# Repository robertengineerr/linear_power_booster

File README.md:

# Linear Power Booster | Guitar Pedal
Linear guitar signal booster with BJT amplification, true bypass switching, and power input protection.

BJT Amplifier
This is the core amplification stage. A single NPN BJT (Q1) amplifies the input signal from a guitar or similar audio source. Capacitors C1 and C2 act as AC coupling (DC-blocking) caps, allowing only the AC signal through. R1 and R2 form a voltage divider to bias the base of Q1, while R3 sets emitter current for gain stability. The amplified signal is output through C2, with a variable resistor (RV1) used to control output volume. This design provides a clean linear boost to the input signal.

Power
This section manages power input and protection. It accepts either a 9V barrel jack or battery input, with diode D2 preventing reverse polarity damage. The capacitor C3 provides basic filtering to smooth out voltage spikes, and the TVS0500DRV IC (U1) protects downstream components from overvoltage by clamping any input above ~9V. The design ensures safe and clean power delivery to the circuit.

Bypass System
This section allows toggling between the amplified signal and the unprocessed (dry) signal. It uses a 3PDT switch (S1) to route the signal either through the amplifier or directly from input to output. Capacitor C4 provides AC coupling for the bypassed signal. This system is commonly used in audio pedals to allow true bypass functionality, preserving the original signal when the effect is disengaged.

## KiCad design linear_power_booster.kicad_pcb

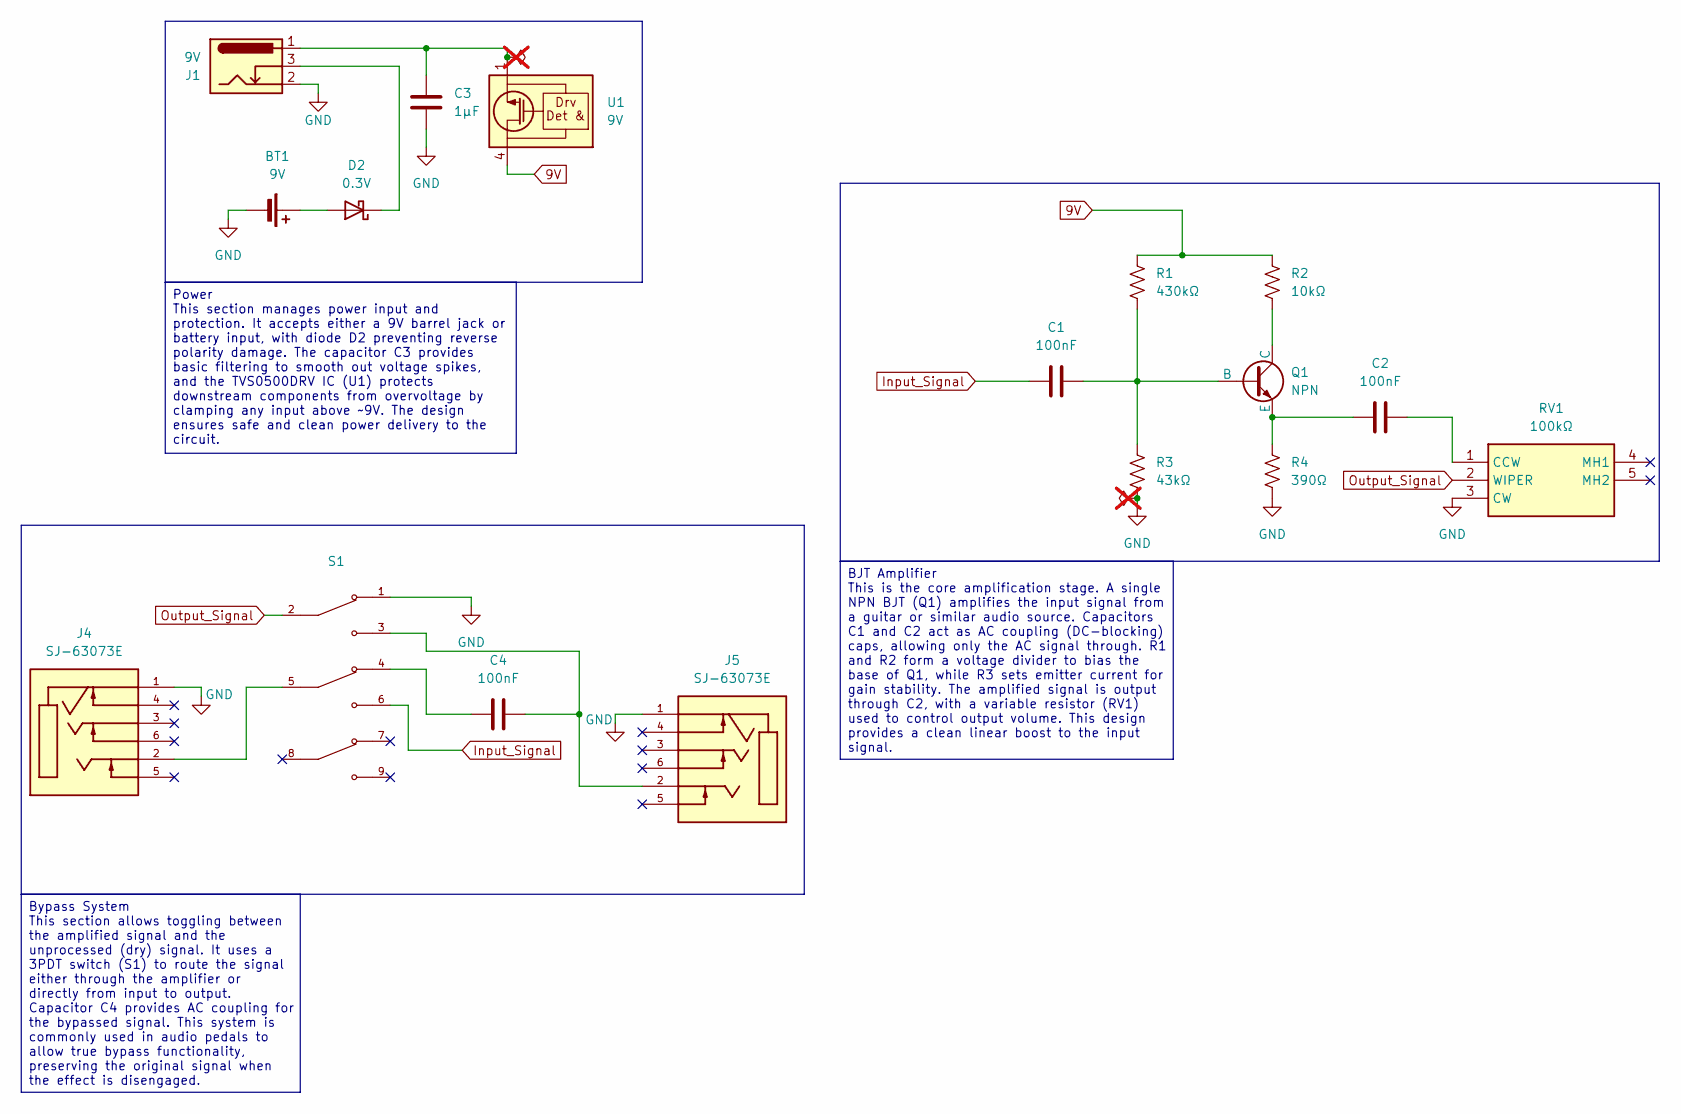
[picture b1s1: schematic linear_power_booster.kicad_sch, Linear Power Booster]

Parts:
BT1: 9V; BatteryHolder_Eagle_12BH611-GR
C1, C2, C4: 100nF; C_Disc_D5.0mm_W2.5mm_P2.50mm
C3: 1µF; C_Disc_D5.0mm_W2.5mm_P2.50mm
D2: 0.3V; D_SMB
J1: 9V; BarrelJack_CUI_PJ-079BH_Horizontal
J4, J5: SJ-63073E; CUI_SJ-63073E; PARTREV 1.0
Q1: NPN; TO-92_Inline
R1: 430kΩ; R_Axial_DIN0207_L6.3mm_D2.5mm_P10.16mm_Horizontal
R2: 10kΩ; R_Axial_DIN0207_L6.3mm_D2.5mm_P10.16mm_Horizontal
R3: 43kΩ; R_Axial_DIN0207_L6.3mm_D2.5mm_P10.16mm_Horizontal
R4: 390Ω; R_Axial_DIN0207_L6.3mm_D2.5mm_P10.16mm_Horizontal
RV1: 100kΩ; PTV09A4030FA104; Mouser Part Number 652-PTV09A4030FA104
S1: FS57003PLT2B2M2QE; SW_FS57003PLT2B2M2QE; PARTREV 4.2.2018
U1: 9V; WSON-6-1EP_2x2mm_P0.65mm_EP1x1.6mm

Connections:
9V: R1.1, R2.1, U1.4 (IN), U1.5 (IN), U1.6 (IN)
GND: BT1.2 (-), C3.2, J1.2, J4.1, J5.1, R3.2, R4.2, RV1.3 (CW), S1.1
Input_Signal: C1.1, S1.6
unnamed: BT1.1 (+), D2.2 (A)
unnamed: C3.1, J1.1, U1.1 (GND), U1.2 (GND), U1.3 (GND), U1.7 (GND)
unnamed: C4.1, S1.4
unnamed: C4.2, J5.2, S1.3
unnamed: D2.1 (K), J1.3
unnamed: J4.2, S1.5
unnamed: C1.2, Q1.2 (B), R1.2, R3.1
unnamed: Q1.1 (C), R2.2
unnamed: C2.1, Q1.3 (E), R4.1
unnamed: C2.2, RV1.1 (CCW)
Output_Signal: RV1.2 (WIPER), S1.2

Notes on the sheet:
Power This section manages power input and protection. It accepts either a 9V barrel jack or battery input, with diode D2 preventing reverse polarity damage. The capacitor C3 provides basic filtering to smooth out voltage spikes, and the TVS0500DRV IC (U1) protects downstream components from overvo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
Bypass System This section allows toggling between the amplified signal and the unprocessed (dry) signal. It uses a 3PDT switch (S1) to route the signal either through the amplifier or directly from input to output. Capacitor C4 provides AC coupling for the bypassed signal. This system is commonly 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
BJT Amplifier This is the core amplification stage. A single NPN BJT (Q1) amplifies the input signal from a guitar or similar audio source. Capacitors C1 and C2 act as AC coupling (DC-blocking) caps, allowing only the AC signal through. R1 and R2 form a voltage divider to bias the base of Q1, while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

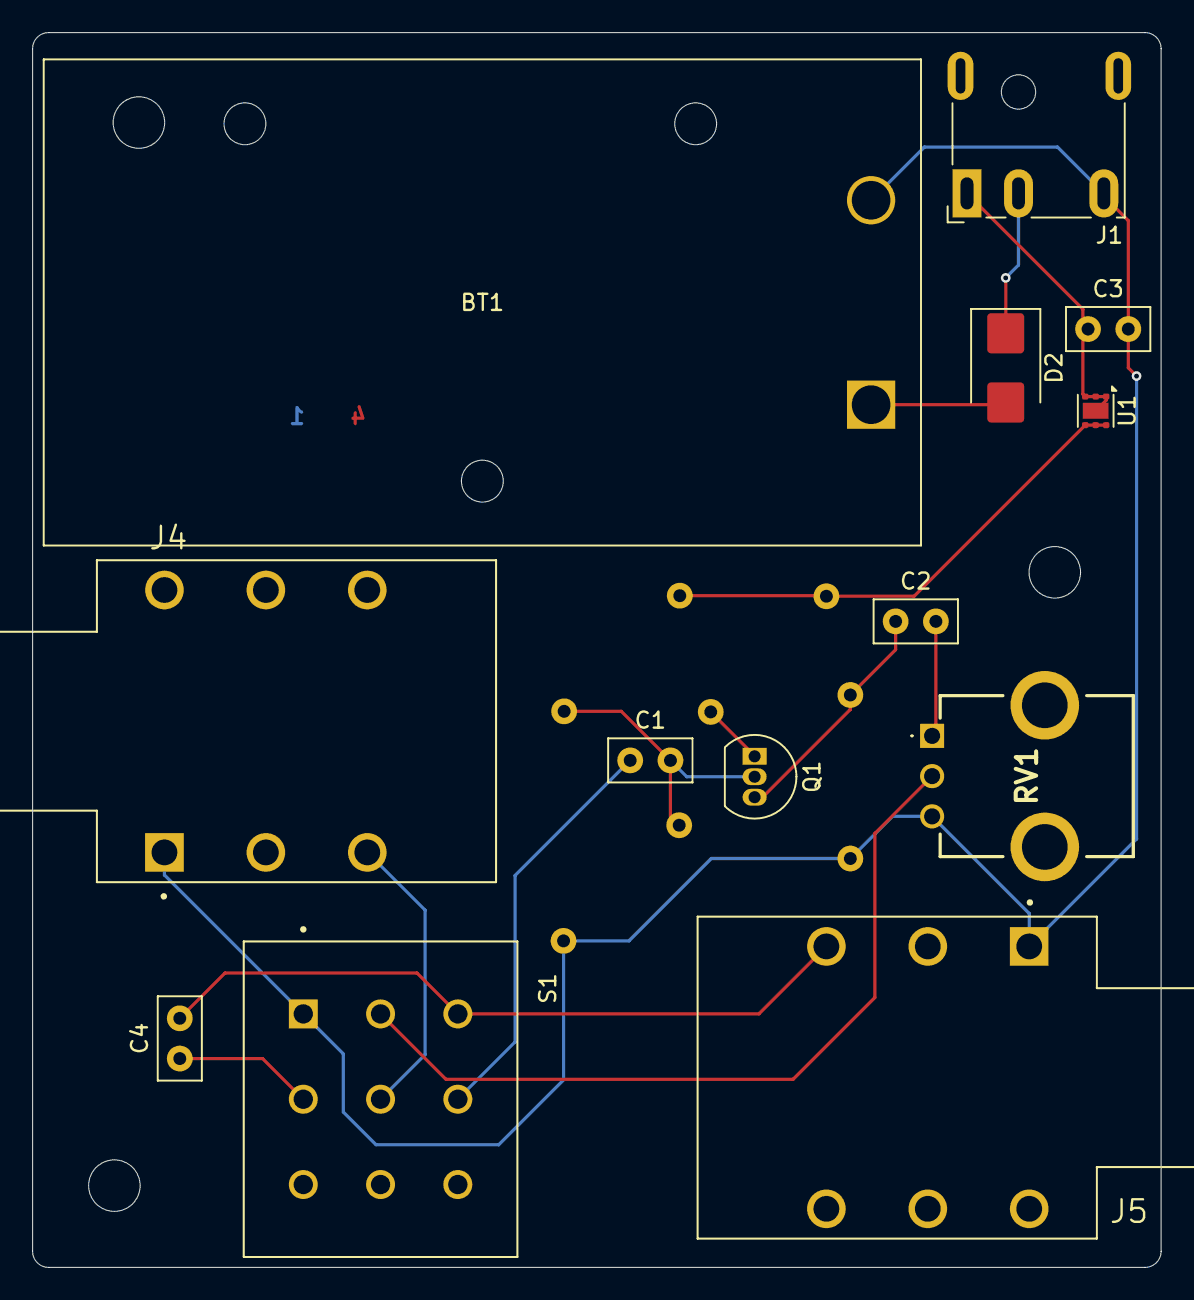
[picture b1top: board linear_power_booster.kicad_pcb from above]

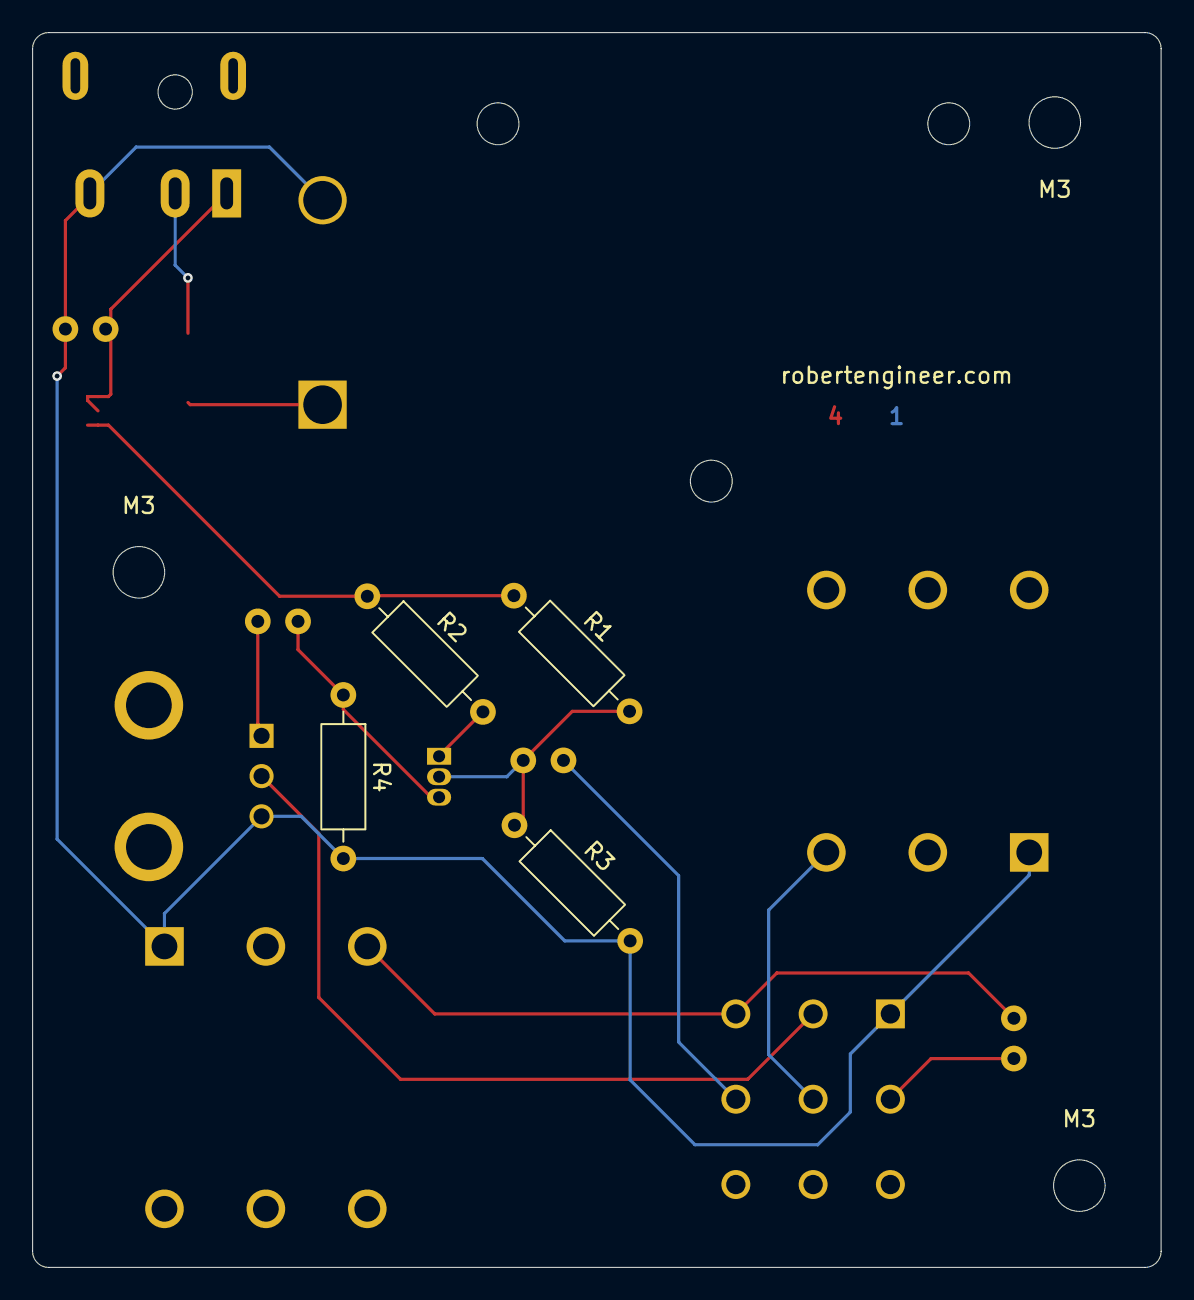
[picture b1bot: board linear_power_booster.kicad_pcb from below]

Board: 2 copper layers, 70.1 x 76.7 mm, 21 parts (6 on the bottom side), 14 nets.

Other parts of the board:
M3, M3#2, M3#3: MountingHole_3.2mm_M3
robertengineer.com: LayerMarker_4_6.35x2.54mm_TextH1mm_P1.27mm
